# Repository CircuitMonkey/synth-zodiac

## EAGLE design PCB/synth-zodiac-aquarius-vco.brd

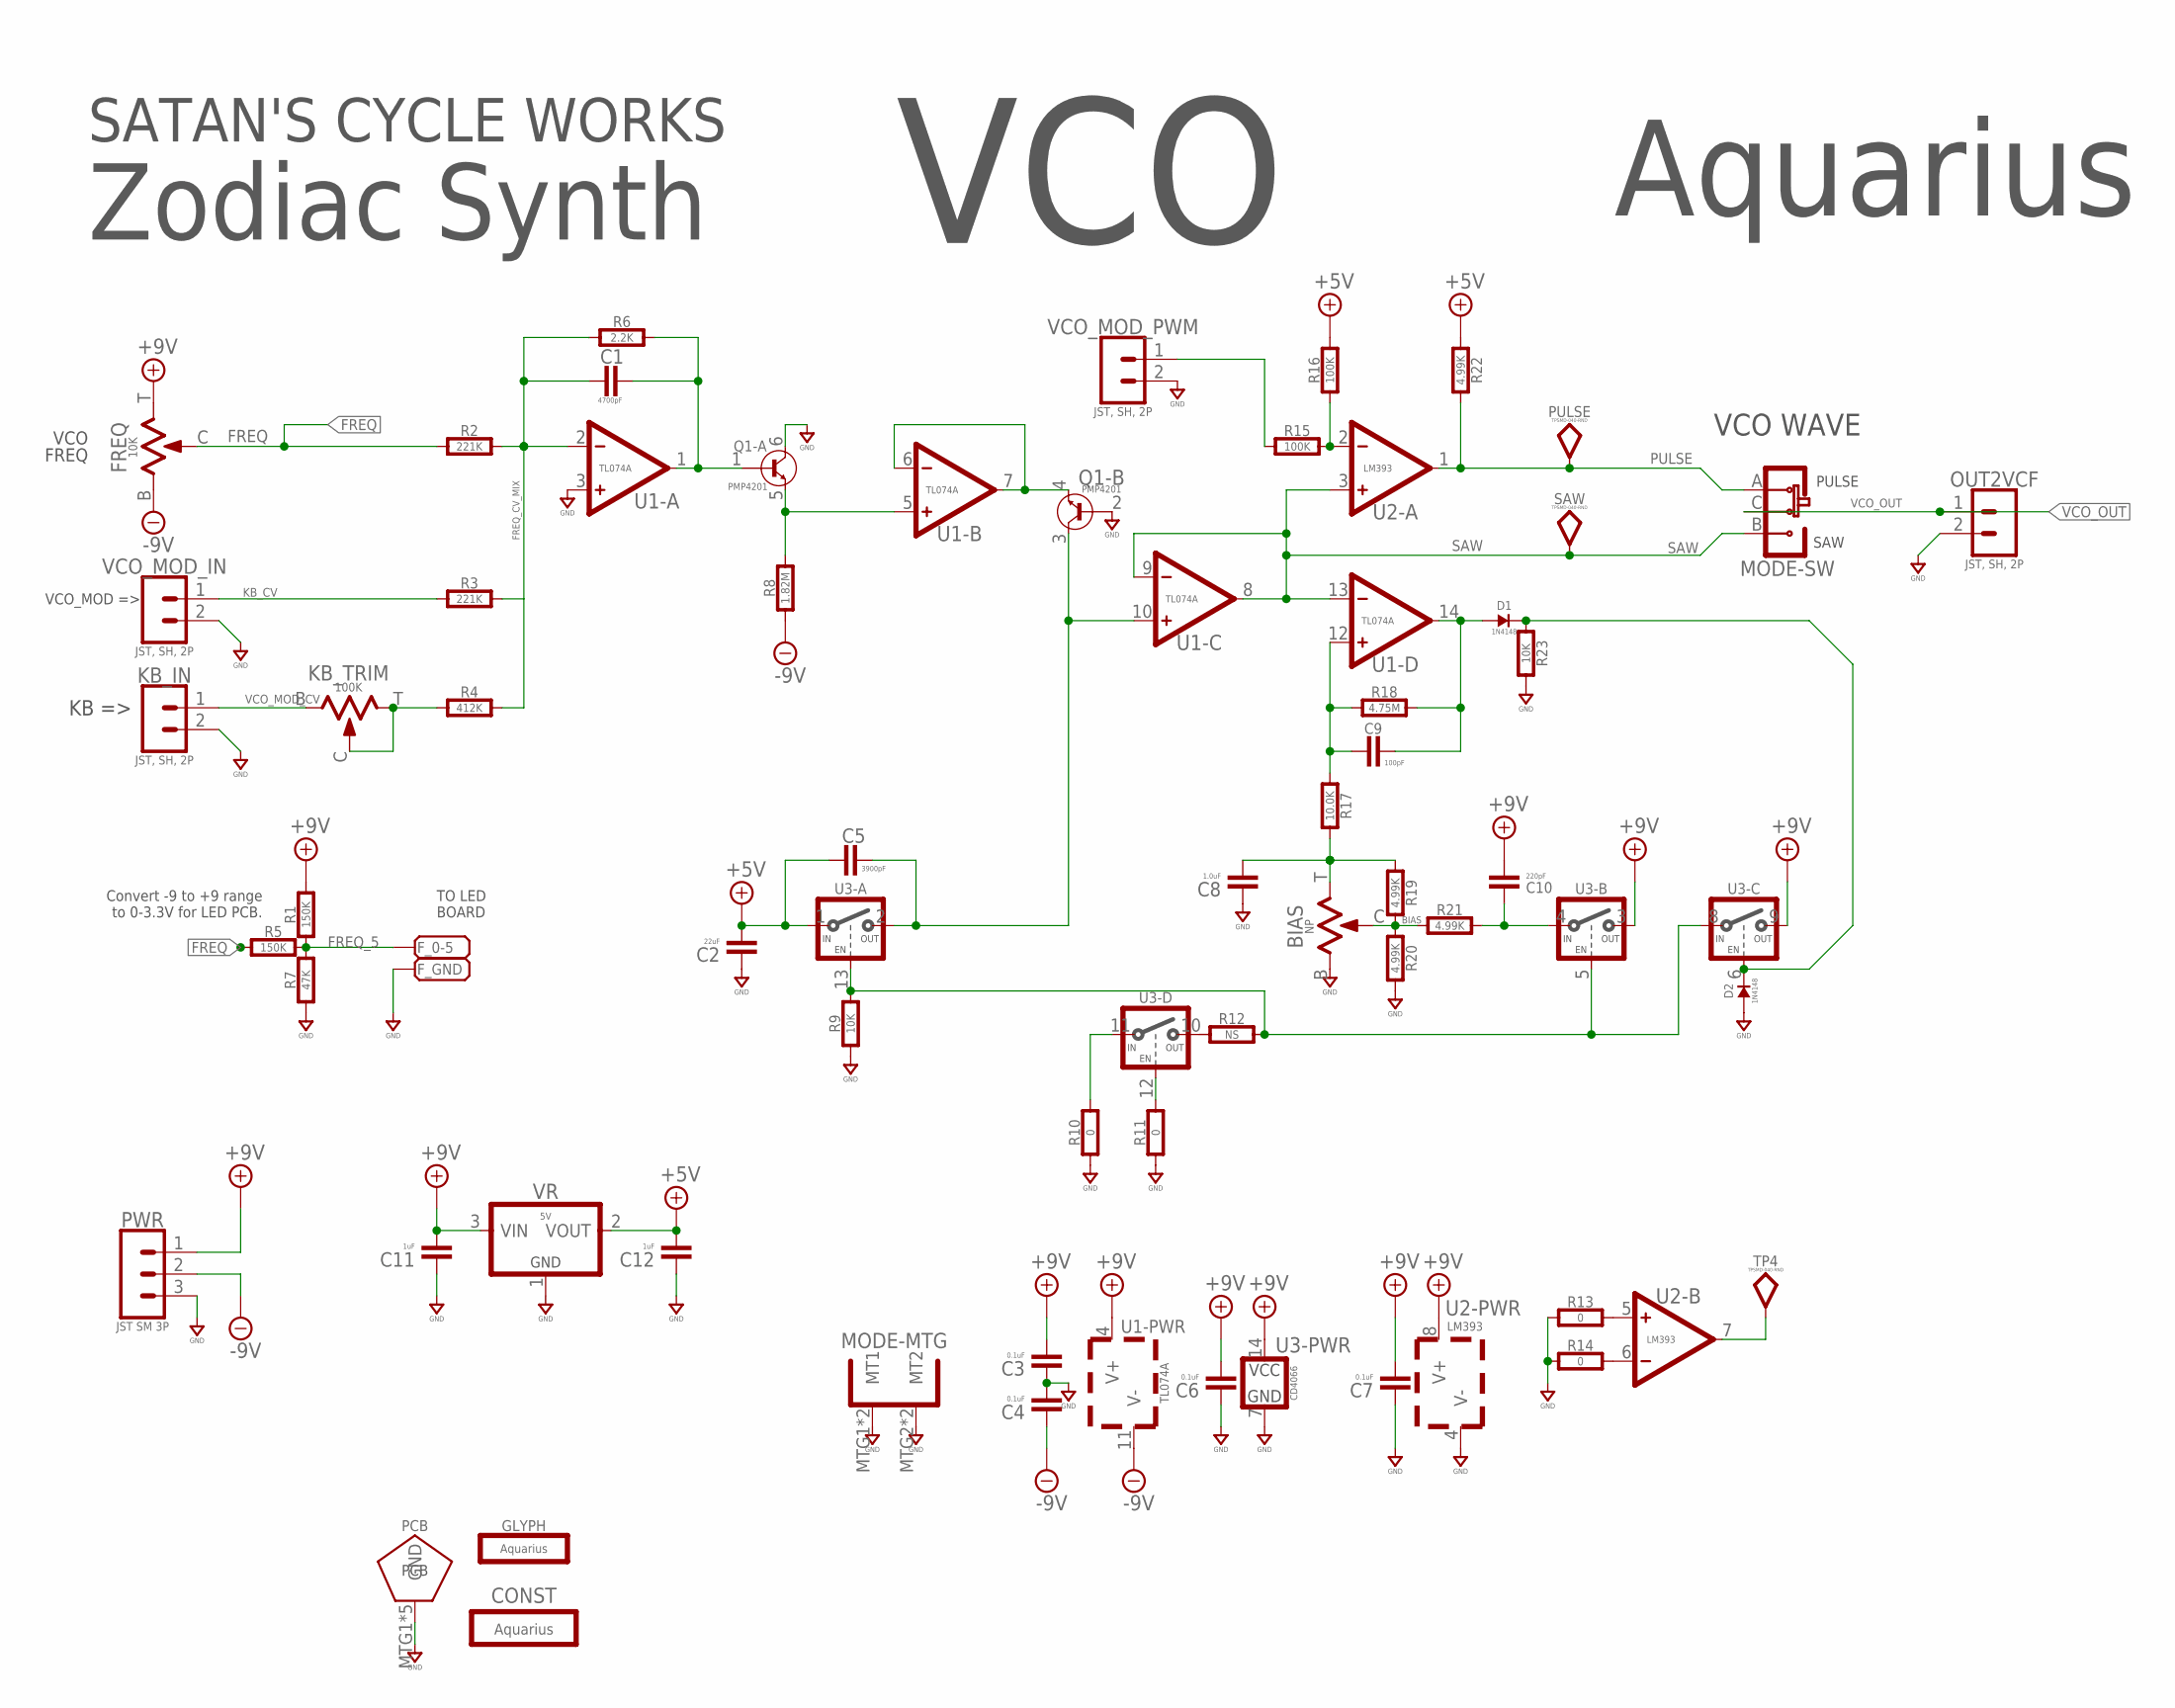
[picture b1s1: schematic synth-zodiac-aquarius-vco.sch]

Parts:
BIAS: NP; TRIM_BOURNS_TC33X
C1: 4700pF; 0603-CAP
C2: 22uF; 0603-CAP
C3, C4, C6, C7: 0.1uF; 0603-CAP
C5: 3900pF; 0603-CAP
C8: 1.0uF; 0603-CAP
C9: 100pF; 0603-CAP
C10: 220pF; 0603-CAP
C11, C12: 1uF; 0603-CAP
CONST: Aquarius; AQUARIUS-CONST
D1, D2: 1N4148; SOD-123
FREQ: 10K; POT-RV9110
F_0-5: PADSMD-070X070; SMD-070MIL
F_GND: PADSMD-070X070; SMD-070MIL
GLYPH: Aquarius; AQUARIUS-GLYPH
KB_IN: JST, SH, 2P; BM02B-SRSS-TB
KB_TRIM: 100K; TRIM_BOURNS_TC33X
MODE: SLIDE-SPDT-MNTSS-12-F45-TH-PCB-2; SS-12-F45-PNL-SMT-2
OUT2VCF: JST, SH, 2P; BM02B-SRSS-TB
PCB: PCB FAB; PENTAGON-40MM-RAD
PULSE: TPSMD-040-RND; SMD-040MIL-RND
PWR: JST SM 3P; BM03B-SRSS-TB
Q1: PMP4201; SOT666
R1, R5: 150K; 0603-RES
R2, R3: 221K; 0603-RES
R4: 412K; 0603-RES
R6: 2.2K; 0603-RES
R7: 47K; 0603-RES
R8: 1.82M; 0603-RES
R9, R23: 10K; 0603-RES
R10, R11, R13, R14: 0; 0603-RES
R12: NS; 0603-RES
R15, R16: 100K; 0603-RES
R17: 10.0K; 0603-RES
R18: 4.75M; 0603-RES
R19, R20, R21, R22: 4.99K; 0603-RES
SAW: TPSMD-040-RND; SMD-040MIL-RND
TP4: TPSMD-040-RND; SMD-040MIL-RND
U1: TL074A; SOP14
U2: LM393; SOP08
U3: CD4066; SOP14
VCO_MOD_IN: JST, SH, 2P; BM02B-SRSS-TB
VCO_MOD_PWM: JST, SH, 2P; BM02B-SRSS-TB
VR: 5V; SOT-23

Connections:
+5V: C2.2, C5.1, C12.2, R16.2, R22.1, U3.1 (IN), VR.2 (VOUT)
+9V: C3.2, C6.2, C7.2, C10.2, C11.2, FREQ.T (3), PWR.1, R1.2, U1.4 (V+), U2.8 (V+), U3.3 (OUT), U3.9 (OUT), U3.14 (VCC), VR.3 (VIN)
-9V: C4.1, FREQ.B (1), PWR.2, R8.1, U1.11 (V-)
BIAS: BIAS.C (2), R19.2, R20.1, R21.1
FREQ: FREQ.C (2), R2.1, R5.1
FREQ_5: F_0-5.1, R1.1, R5.2, R7.2
FREQ_CV_MIX: C1.1, R2.2, R3.2, R4.2, R6.1, U1.2 (-)
GND: BIAS.B (1), C2.1, C3.1, C4.2, C6.1, C7.1, C8.1, C11.1, C12.1, D2.A, F_GND.1, KB_IN.2, MODE.MTG1 (MT1), MODE.MTG2 (MT2), MODE.MTG3 (MT1), MODE.MTG4 (MT2), OUT2VCF.2, PCB.MTG1, PCB.MTG2, PCB.MTG3, PCB.MTG4, PCB.MTG5, PWR.3, Q1.2 (BASE), Q1.6 (COLLECTOR), R7.1, R9.1, R10.1, R11.1, R13.1, R14.1, R20.2, R23.2, U1.3 (+), U2.4 (V-), U3.7 (GND), VCO_MOD_IN.2, VCO_MOD_PWM.2, VR.1 (GND)
KB_CV: KB_IN.1, KB_TRIM.B (1)
unnamed: KB_TRIM.C (2), KB_TRIM.T (3), R4.1
unnamed: Q1.5 (EMITTER), R8.2, U1.5 (+)
unnamed: Q1.4 (EMITTER), U1.6 (-), U1.7 (OUT)
unnamed: C1.2, Q1.1 (BASE), R6.2, U1.1 (OUT)
unnamed: R9.2, R12.2, U3.5 (EN), U3.8 (IN), U3.13 (EN)
unnamed: C9.1, R17.1, R18.1, U1.12 (+)
unnamed: R14.2, U2.6 (-)
unnamed: C9.2, D1.A, R18.2, U1.14 (OUT)
unnamed: C5.2, Q1.3 (COLLECTOR), U1.10 (+), U3.2 (OUT)
unnamed: BIAS.T (3), C8.2, R17.2, R19.1
unnamed: C10.1, R21.2, U3.4 (IN)
unnamed: R12.1, U3.10 (OUT)
unnamed: D1.K, D2.K, R23.1, U3.6 (EN)
unnamed: R10.2, U3.11 (IN)
unnamed: R11.2, U3.12 (EN)
unnamed: R13.2, U2.5 (+)
unnamed: R15.2, R16.1, U2.2 (-)
unnamed: TP4.TP, U2.7 (OUT)
PULSE: MODE.A, PULSE.TP, R22.2, U2.1 (OUT)
PWM_CV: R15.1, VCO_MOD_PWM.1
SAW: MODE.B, SAW.TP, U1.8 (OUT), U1.9 (-), U1.13 (-), U2.3 (+)
VCO_MOD_CV: R3.1, VCO_MOD_IN.1
VCO_OUT: MODE.C, OUT2VCF.1

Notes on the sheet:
VCO FREQ
VCO WAVE
VCO
PULSE
SAW
KB =>
VCO_MOD =>
Zodiac Synth
Aquarius
TO LED BOARD
Convert -9 to +9 range to 0-3.3V for LED PCB.
SATAN'S CYCLE WORKS

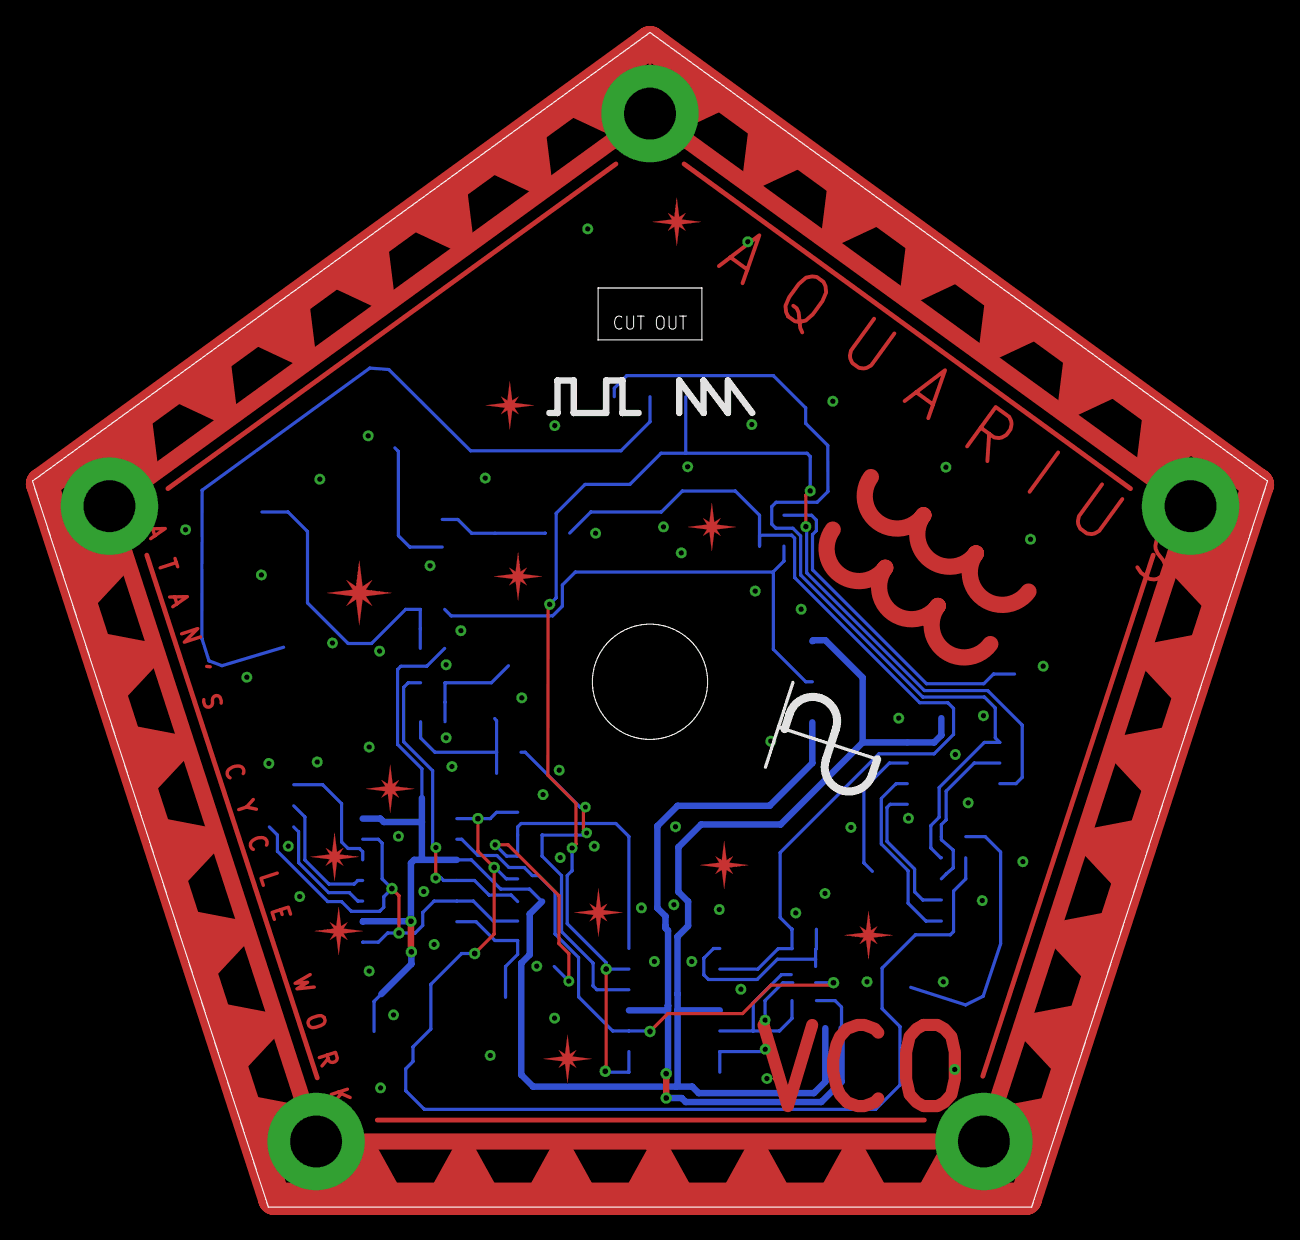
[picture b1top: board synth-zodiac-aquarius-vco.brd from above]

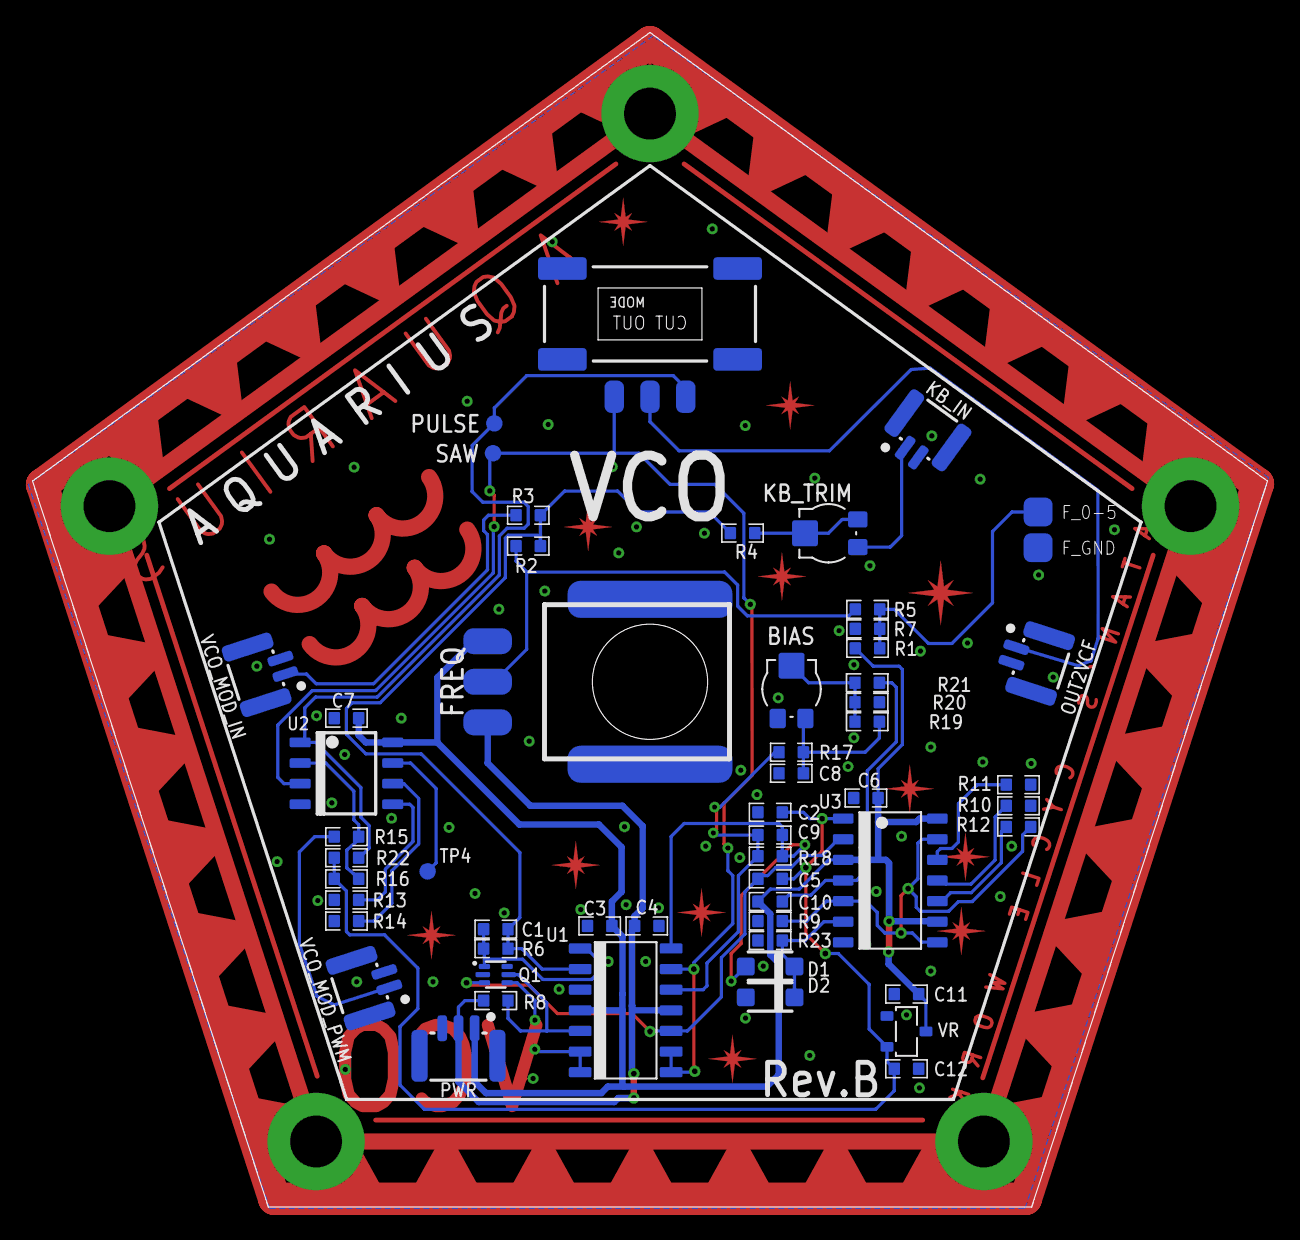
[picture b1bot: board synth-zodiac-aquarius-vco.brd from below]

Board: 2 copper layers, 76.1 x 72.4 mm, 59 parts (55 on the bottom side), 32 nets.

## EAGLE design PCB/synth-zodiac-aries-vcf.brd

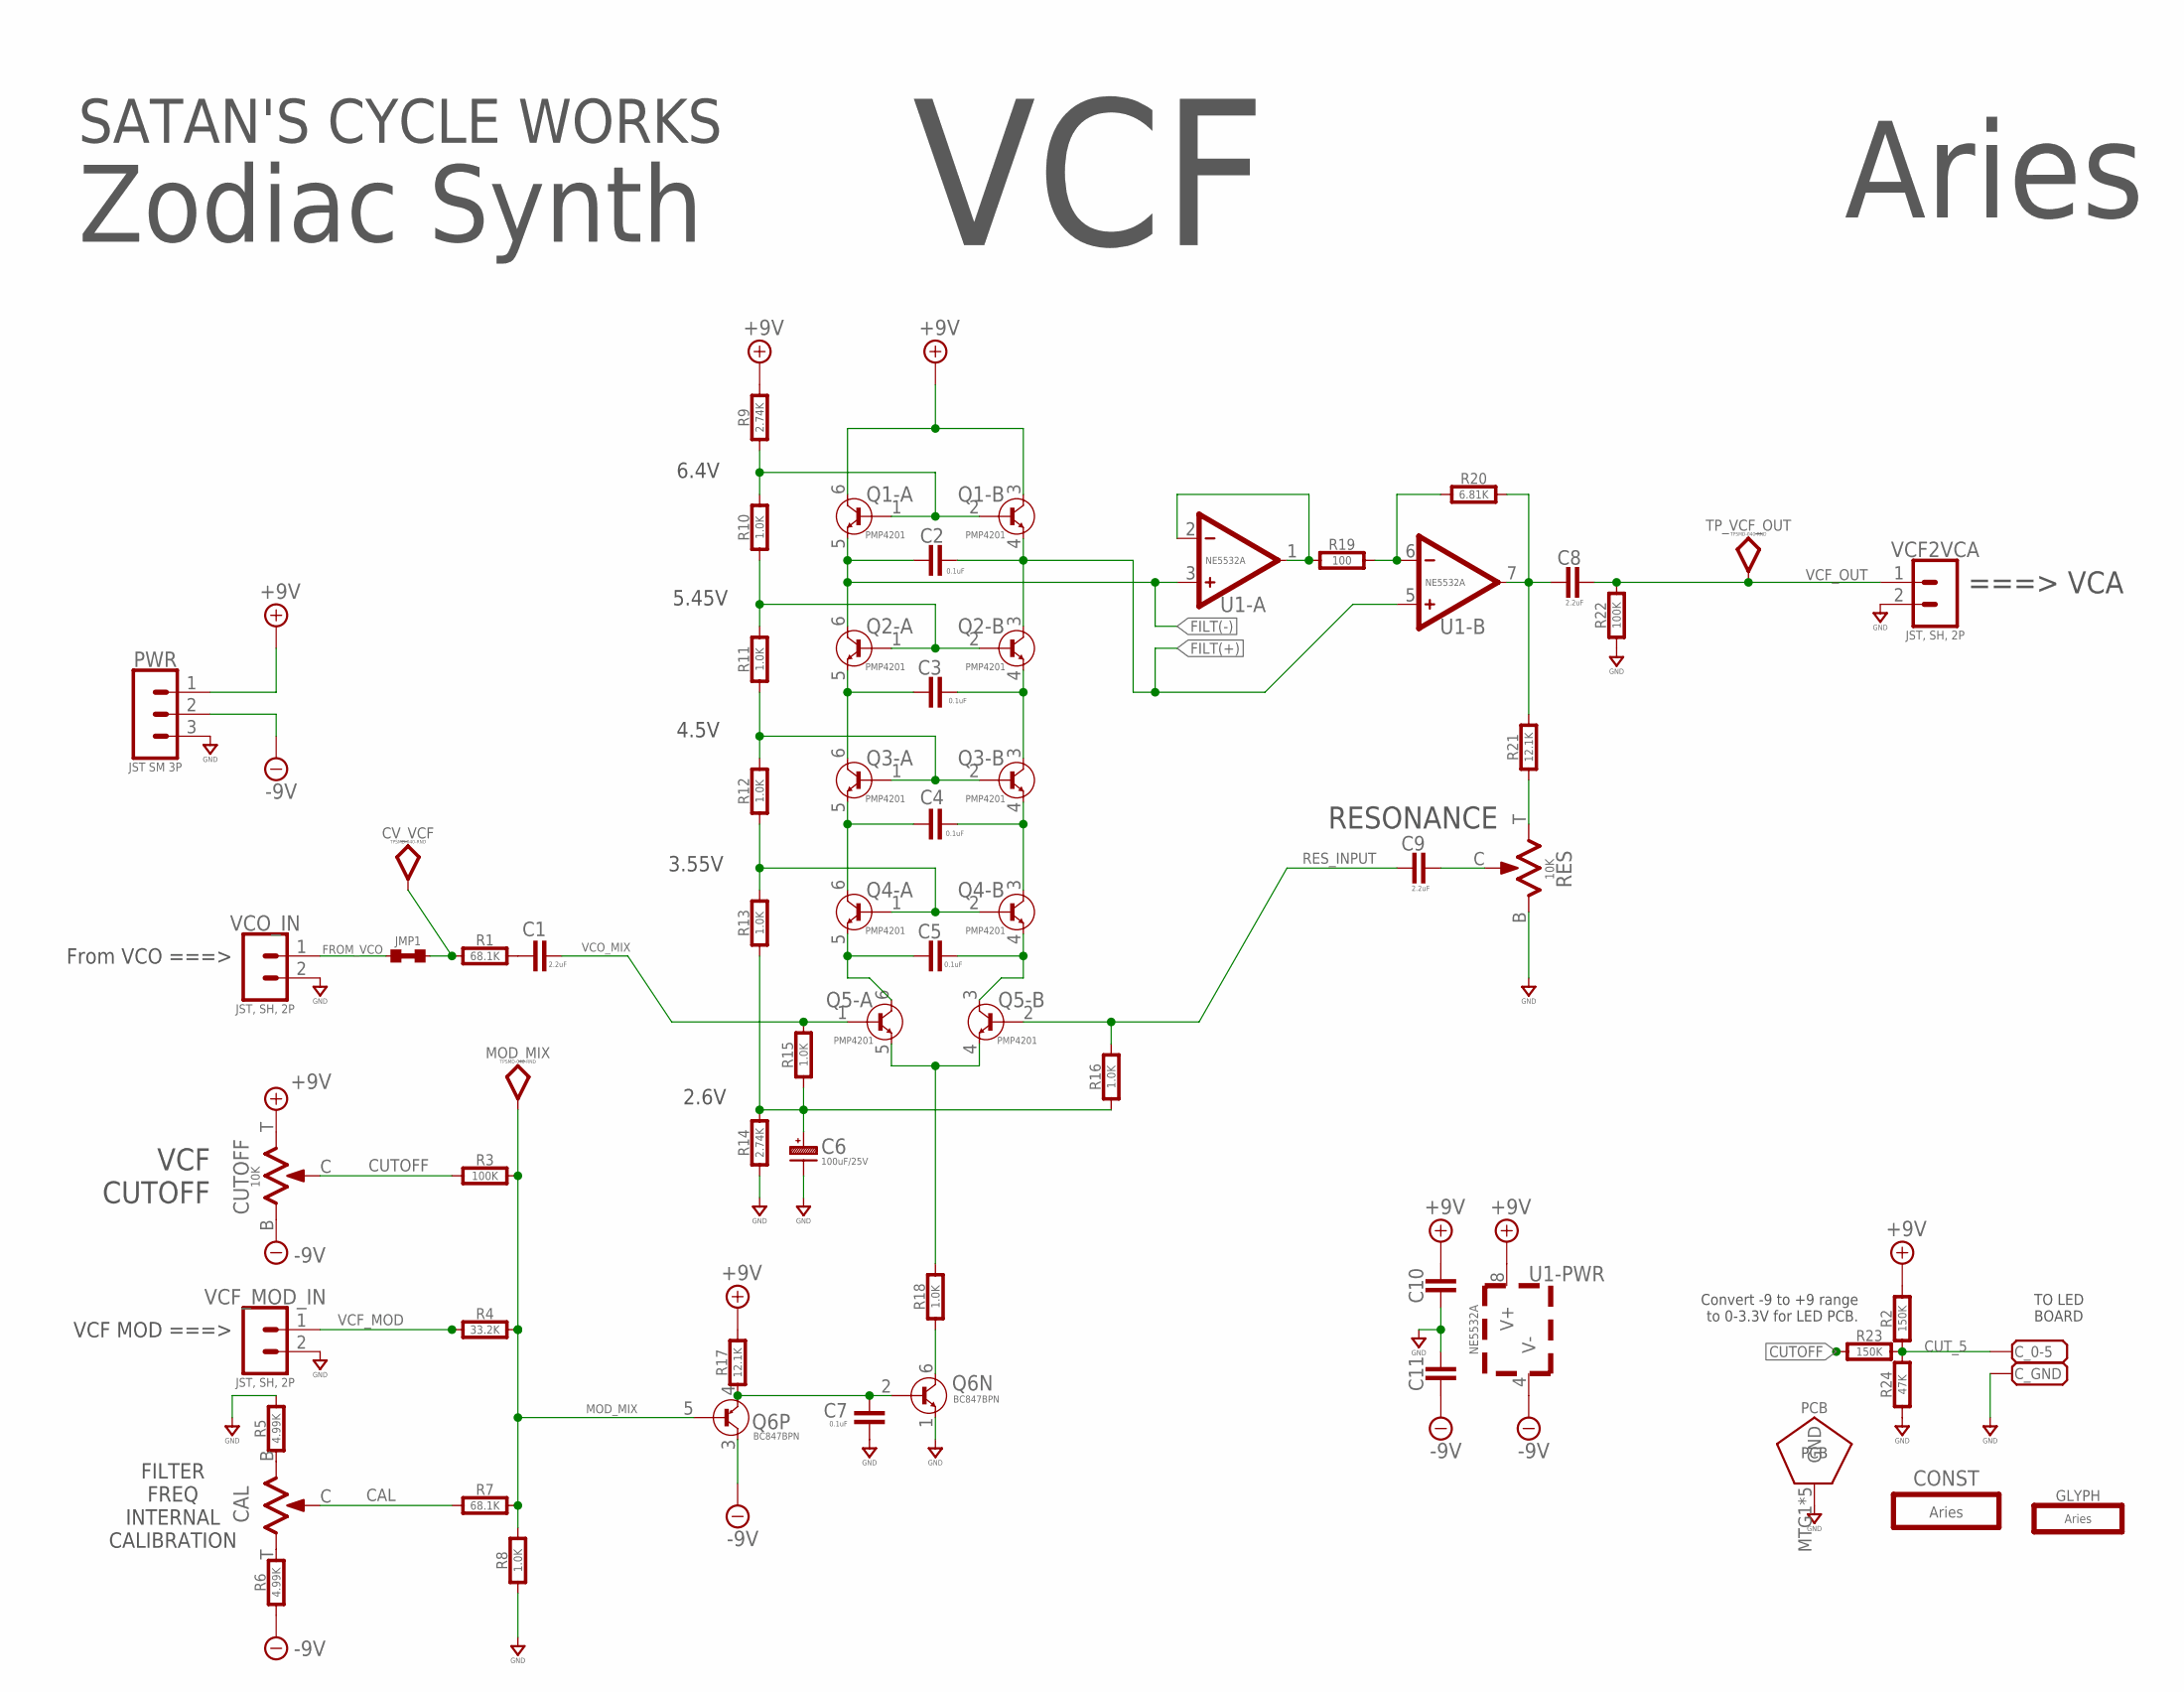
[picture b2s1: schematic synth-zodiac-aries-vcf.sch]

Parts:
C1, C8, C9: 2.2uF; 0603-CAP
C2, C3, C4, C5, C7, C10, C11: 0.1uF; 0603-CAP
C6: 100uF/25V; CAP_ALUM_SMT_6.3; MPN 865090445008
CAL: 10K; TRIM_BOURNS_TC33X
CONST: Aries; ARIES-CONST
CUTOFF: 10K; POT-RV9110
CV_VCF: TPSMD-040-RND; SMD-040MIL-RND
C_0-5: PADSMD-070X070; SMD-070MIL
C_GND: PADSMD-070X070; SMD-070MIL
GLYPH: Aries; ARIES-GLYPH
JMP1: NP; 0603-SHORT
MOD_MIX: TPSMD-040-RND; SMD-040MIL-RND
PCB: PCB FAB; PENTAGON-40MM-RAD
PWR: JST SM 3P; BM03B-SRSS-TB
Q1, Q2, Q3, Q4, Q5: PMP4201; SOT666
Q6: BC847BPN; SOT363
R1, R7: 68.1K; 0603-RES
R2, R23: 150K; 0603-RES
R3, R22: 100K; 0603-RES
R4: 33.2K; 0603-RES
R5, R6: 4.99K; 0603-RES
R8, R10, R11, R12, R13, R15, R16, R18: 1.0K; 0603-RES
R9, R14: 2.74K; 0603-RES
R17, R21: 12.1K; 0603-RES
R19: 100; 0603-RES
R20: 6.81K; 0603-RES
R24: 47K; 0603-RES
RES: 10K; POT-RV9110
TP_VCF_OUT: TPSMD-040-RND; SMD-040MIL-RND
U1: NE5532A; SOP08
VCF2VCA: JST, SH, 2P; BM02B-SRSS-TB
VCF_MOD_IN: JST, SH, 2P; BM02B-SRSS-TB
VCO_IN: JST, SH, 2P; BM02B-SRSS-TB

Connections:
+9V: C10.2, CUTOFF.T (3), PWR.1, Q1.3 (COLLECTOR), Q1.6 (COLLECTOR), R2.2, R9.2, R17.2, U1.8 (V+)
-9V: C11.1, CUTOFF.B (1), PWR.2, Q6.3 (COLLECTOR), R6.1, U1.4 (V-)
CAL: CAL.C (2), R7.1
CUTOFF: CUTOFF.C (2), R3.1, R23.1
CUT_5: C_0-5.1, R2.1, R23.2, R24.2
FILT(+): C2.2, Q1.4 (EMITTER), Q2.3 (COLLECTOR), U1.5 (+)
FILT(-): C2.1, Q1.5 (EMITTER), Q2.6 (COLLECTOR), U1.3 (+)
FROM_VCO: JMP1.3 (1), VCO_IN.1
GND: C6.- (N), C7.2, C10.1, C11.2, C_GND.1, PCB.MTG1, PCB.MTG2, PCB.MTG3, PCB.MTG4, PCB.MTG5, PWR.3, Q6.1 (EMITTER), R5.2, R8.1, R14.1, R22.1, R24.1, RES.B (1), VCF2VCA.2, VCF_MOD_IN.2, VCO_IN.2
MOD_MIX: MOD_MIX.TP, Q6.5 (BASE), R3.2, R4.2, R7.2, R8.2
unnamed: R19.2, R20.1, U1.6 (-)
unnamed: Q1.1 (BASE), Q1.2 (BASE), R9.1, R10.2
unnamed: C3.1, Q2.5 (EMITTER), Q3.6 (COLLECTOR)
unnamed: C3.2, Q2.4 (EMITTER), Q3.3 (COLLECTOR)
unnamed: Q2.1 (BASE), Q2.2 (BASE), R10.1, R11.2
unnamed: C4.1, Q3.5 (EMITTER), Q4.6 (COLLECTOR)
unnamed: C4.2, Q3.4 (EMITTER), Q4.3 (COLLECTOR)
unnamed: Q3.1 (BASE), Q3.2 (BASE), R11.1, R12.2
unnamed: C5.1, Q4.5 (EMITTER), Q5.6 (COLLECTOR)
unnamed: C5.2, Q4.4 (EMITTER), Q5.3 (COLLECTOR)
unnamed: Q4.1 (BASE), Q4.2 (BASE), R12.1, R13.2
unnamed: Q5.4 (EMITTER), Q5.5 (EMITTER), R18.2
unnamed: Q6.6 (COLLECTOR), R18.1
unnamed: C6.+, R13.1, R14.2, R15.1, R16.1
unnamed: C7.1, Q6.2 (BASE), Q6.4 (EMITTER), R17.1
unnamed: CAL.T (3), R6.2
unnamed: CAL.B (1), R5.1
unnamed: C1.1, R1.2
unnamed: R19.1, U1.1 (OUT), U1.2 (-)
unnamed: C8.1, R20.2, R21.2, U1.7 (OUT)
unnamed: R21.1, RES.T (3)
unnamed: C9.2, RES.C (2)
RES_INPUT: C9.1, Q5.2 (BASE), R16.2
VCF_IN: CV_VCF.TP, JMP1.4 (2), R1.1
VCF_MOD: R4.1, VCF_MOD_IN.1
VCF_OUT: C8.2, R22.2, TP_VCF_OUT.TP, VCF2VCA.1
VCO_MIX: C1.2, Q5.1 (BASE), R15.2

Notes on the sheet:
FILTER FREQ INTERNAL CALIBRATION
RESONANCE
VCF CUTOFF
===> VCA
From VCO ===>
VCF MOD ===>
6.4V
5.45V
4.5V
3.55V
2.6V
TO LED BOARD
Convert -9 to +9 range to 0-3.3V for LED PCB.
VCF
Zodiac Synth
Aries
SATAN'S CYCLE WORKS

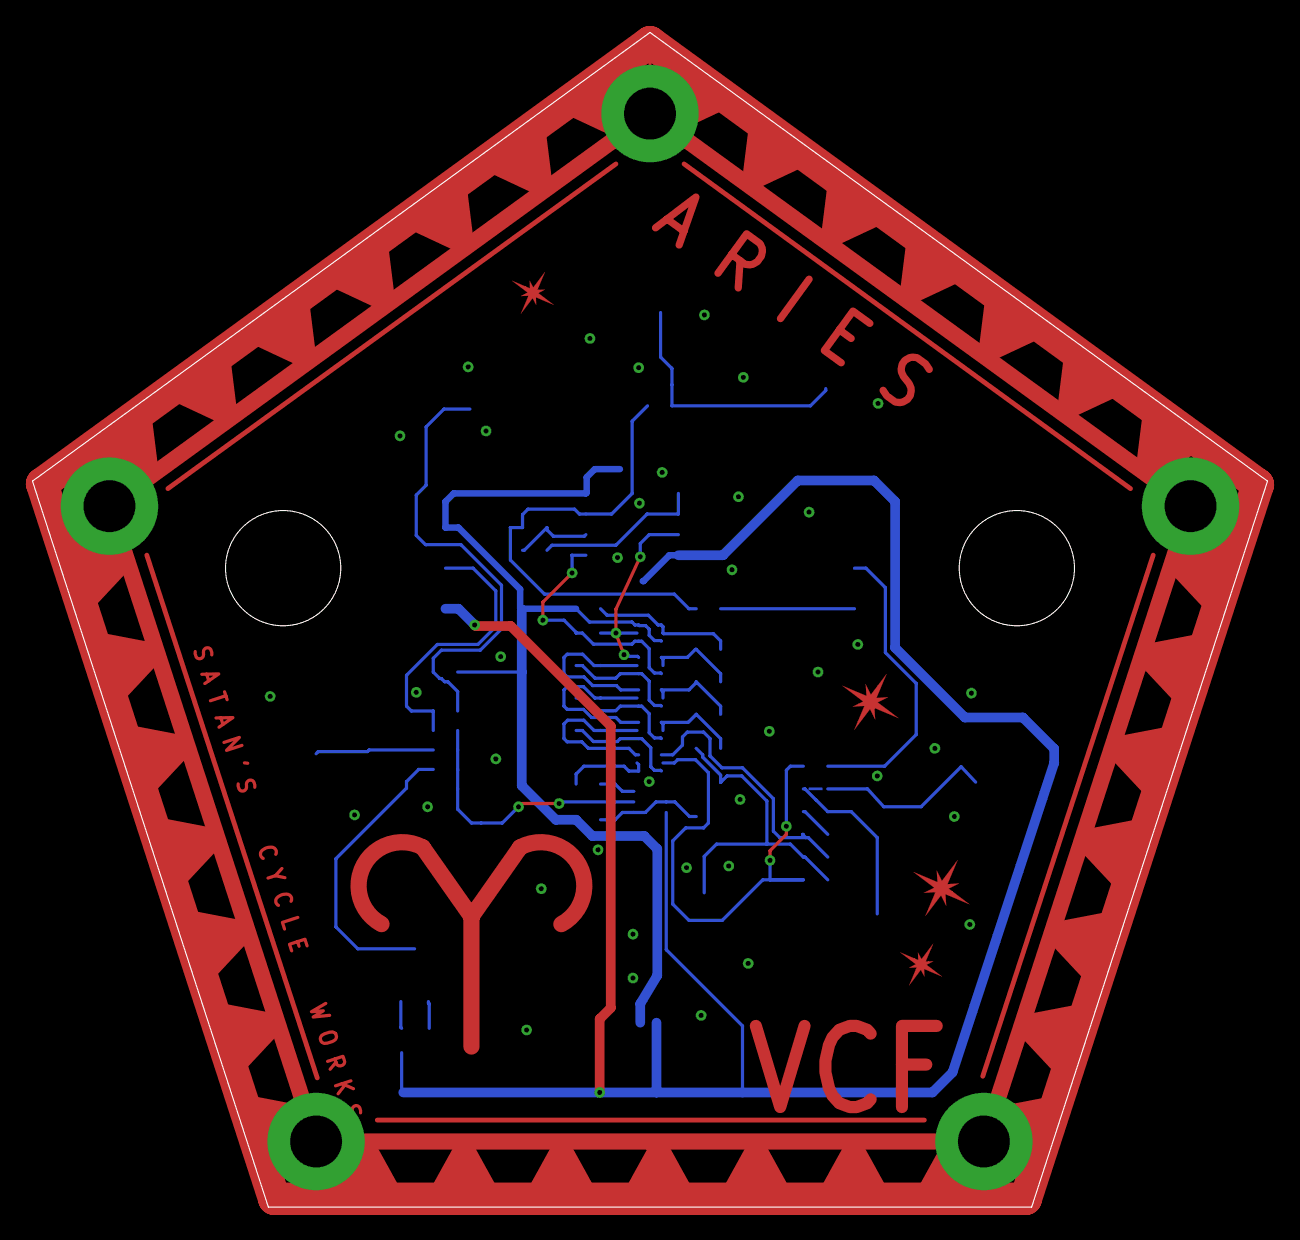
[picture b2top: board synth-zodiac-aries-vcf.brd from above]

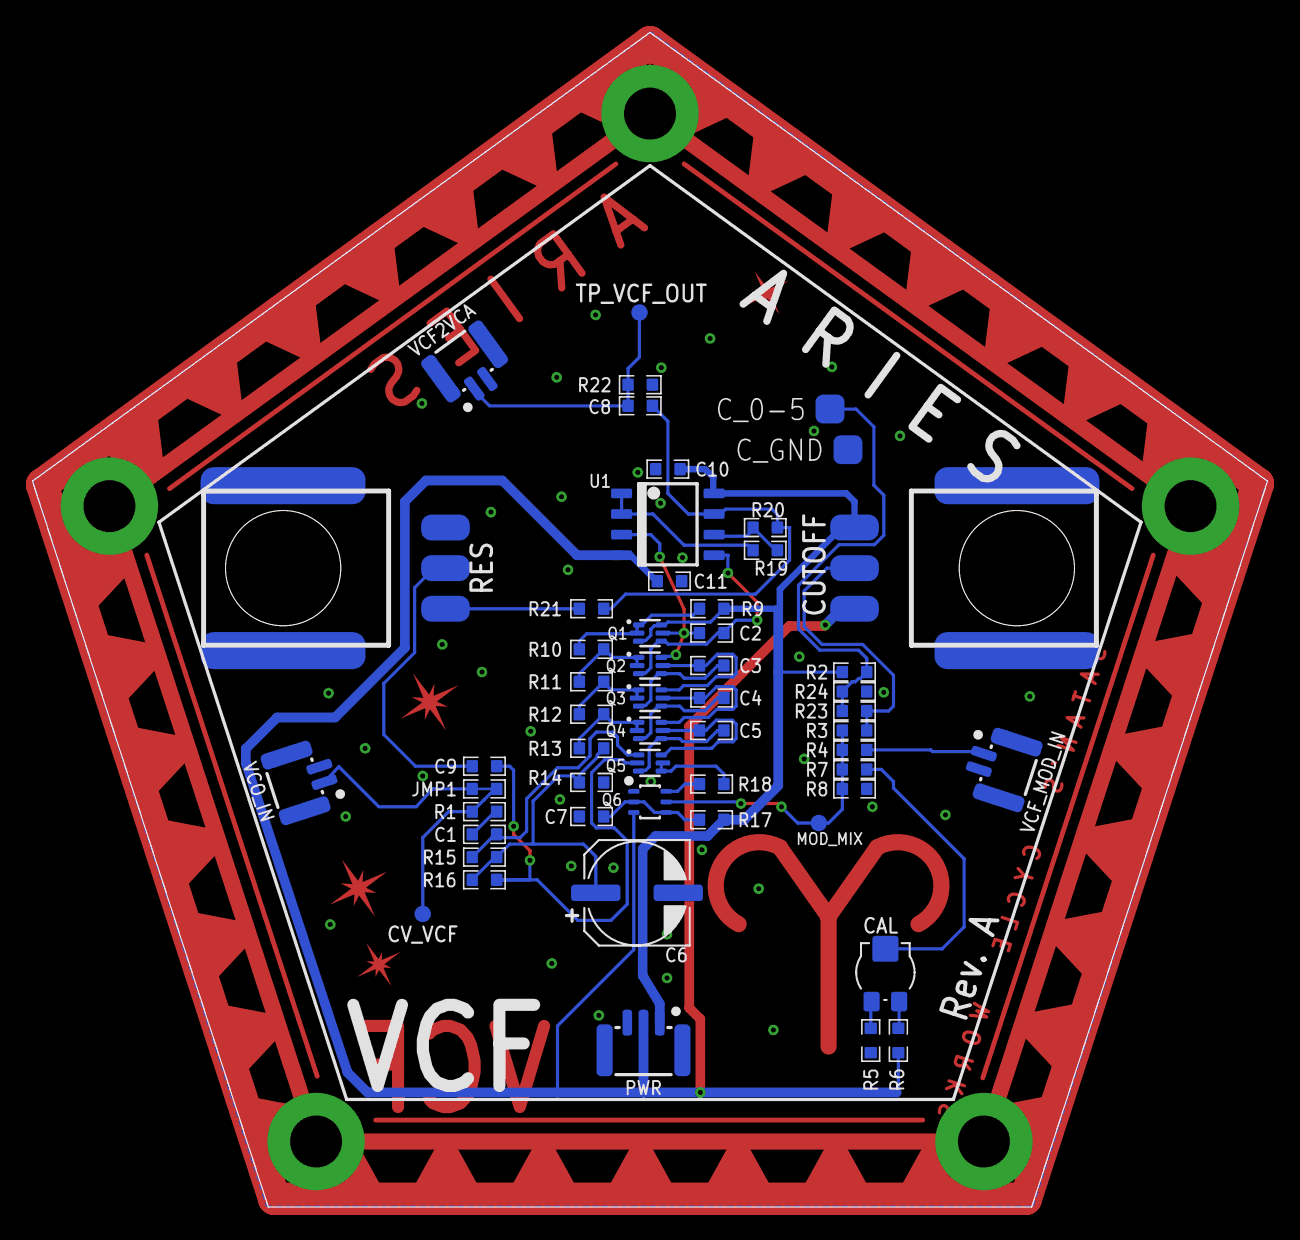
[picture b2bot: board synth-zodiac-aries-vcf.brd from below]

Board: 2 copper layers, 76.1 x 72.4 mm, 58 parts (55 on the bottom side), 37 nets.

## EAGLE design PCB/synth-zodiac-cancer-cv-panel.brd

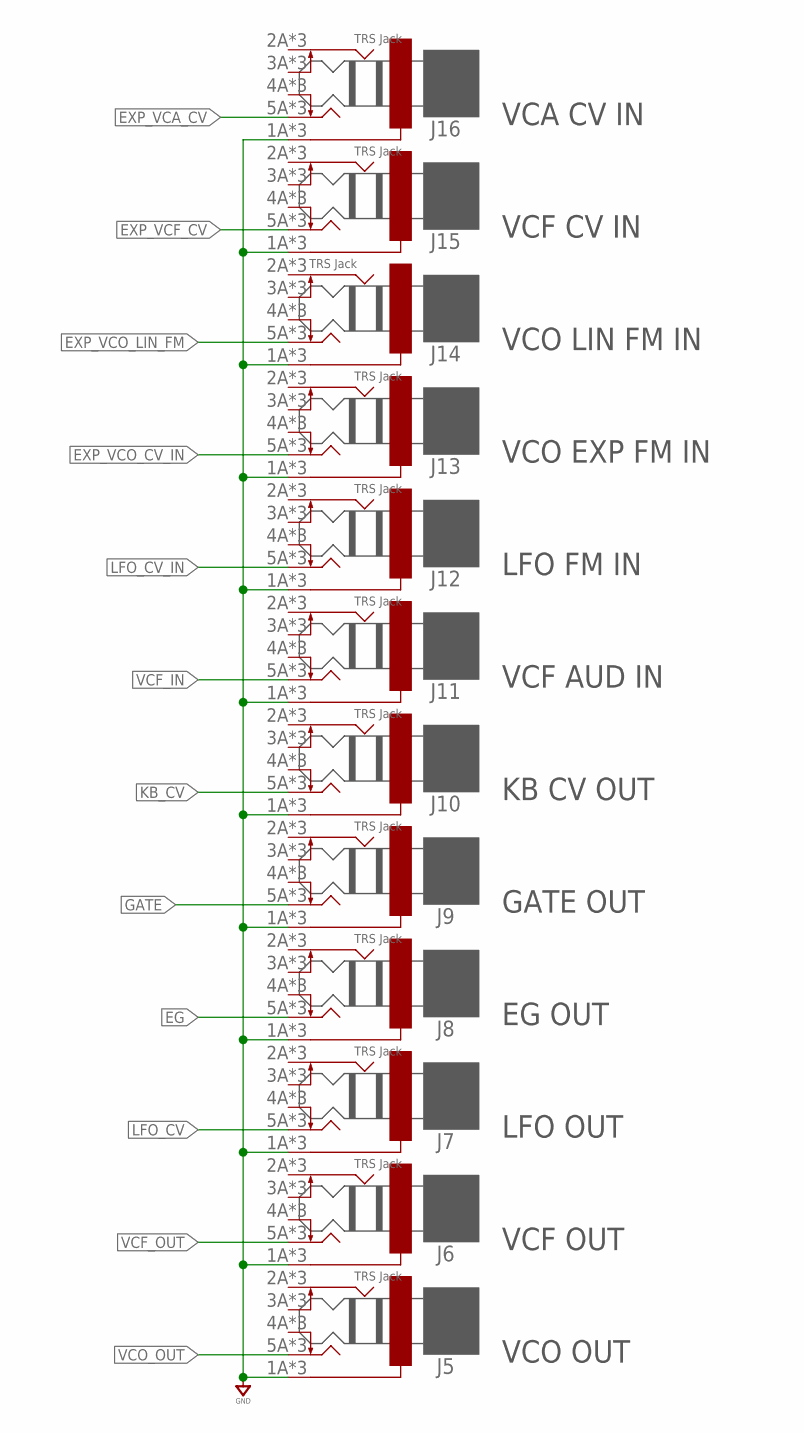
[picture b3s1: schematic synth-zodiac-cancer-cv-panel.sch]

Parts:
J5, J6, J7, J8, J9, J10, J11, J12, J13, J14, J15, J16: TRS Jack; PJ-324

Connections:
EG: J8.5A (T), J8.5A1 (T), J8.5A2 (T)
EXP_VCA_CV: J16.5A (T), J16.5A1 (T), J16.5A2 (T)
EXP_VCF_CV: J15.5A (T), J15.5A1 (T), J15.5A2 (T)
EXP_VCO_CV_IN: J13.5A (T), J13.5A1 (T), J13.5A2 (T)
EXP_VCO_LIN_FM: J14.5A (T), J14.5A1 (T), J14.5A2 (T)
GATE: J9.5A (T), J9.5A1 (T), J9.5A2 (T)
GND: J5.1A (S), J5.1A1 (S), J5.1A2 (S), J6.1A (S), J6.1A1 (S), J6.1A2 (S), J7.1A (S), J7.1A1 (S), J7.1A2 (S), J8.1A (S), J8.1A1 (S), J8.1A2 (S), J9.1A (S), J9.1A1 (S), J9.1A2 (S), J10.1A (S), J10.1A1 (S), J10.1A2 (S), J11.1A (S), J11.1A1 (S), J11.1A2 (S), J12.1A (S), J12.1A1 (S), J12.1A2 (S), J13.1A (S), J13.1A1 (S), J13.1A2 (S), J14.1A (S), J14.1A1 (S), J14.1A2 (S), J15.1A (S), J15.1A1 (S), J15.1A2 (S), J16.1A (S), J16.1A1 (S), J16.1A2 (S)
KB_CV: J10.5A (T), J10.5A1 (T), J10.5A2 (T)
LFO_CV: J7.5A (T), J7.5A1 (T), J7.5A2 (T)
LFO_CV_IN: J12.5A (T), J12.5A1 (T), J12.5A2 (T)
VCF_IN: J11.5A (T), J11.5A1 (T), J11.5A2 (T)
VCF_OUT: J6.5A (T), J6.5A1 (T), J6.5A2 (T)
VCO_OUT: J5.5A (T), J5.5A1 (T), J5.5A2 (T)

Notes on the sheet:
VCA CV IN VCF CV IN VCO LIN FM IN VCO EXP FM IN LFO FM IN VCF AUD IN KB CV OUT GATE OUT EG OUT LFO OUT VCF OUT VCO OUT

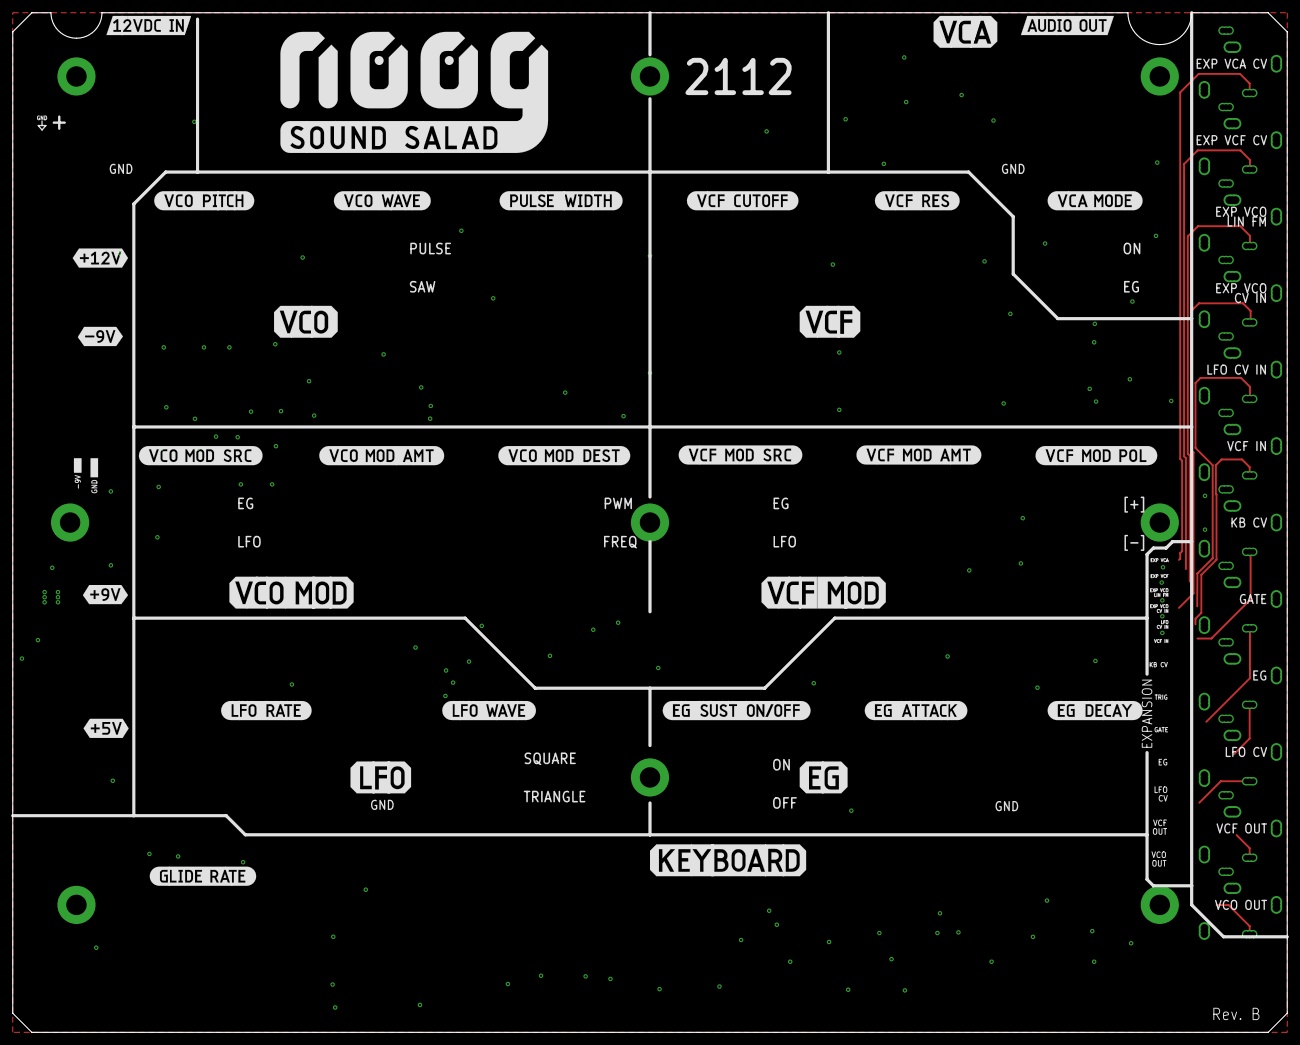
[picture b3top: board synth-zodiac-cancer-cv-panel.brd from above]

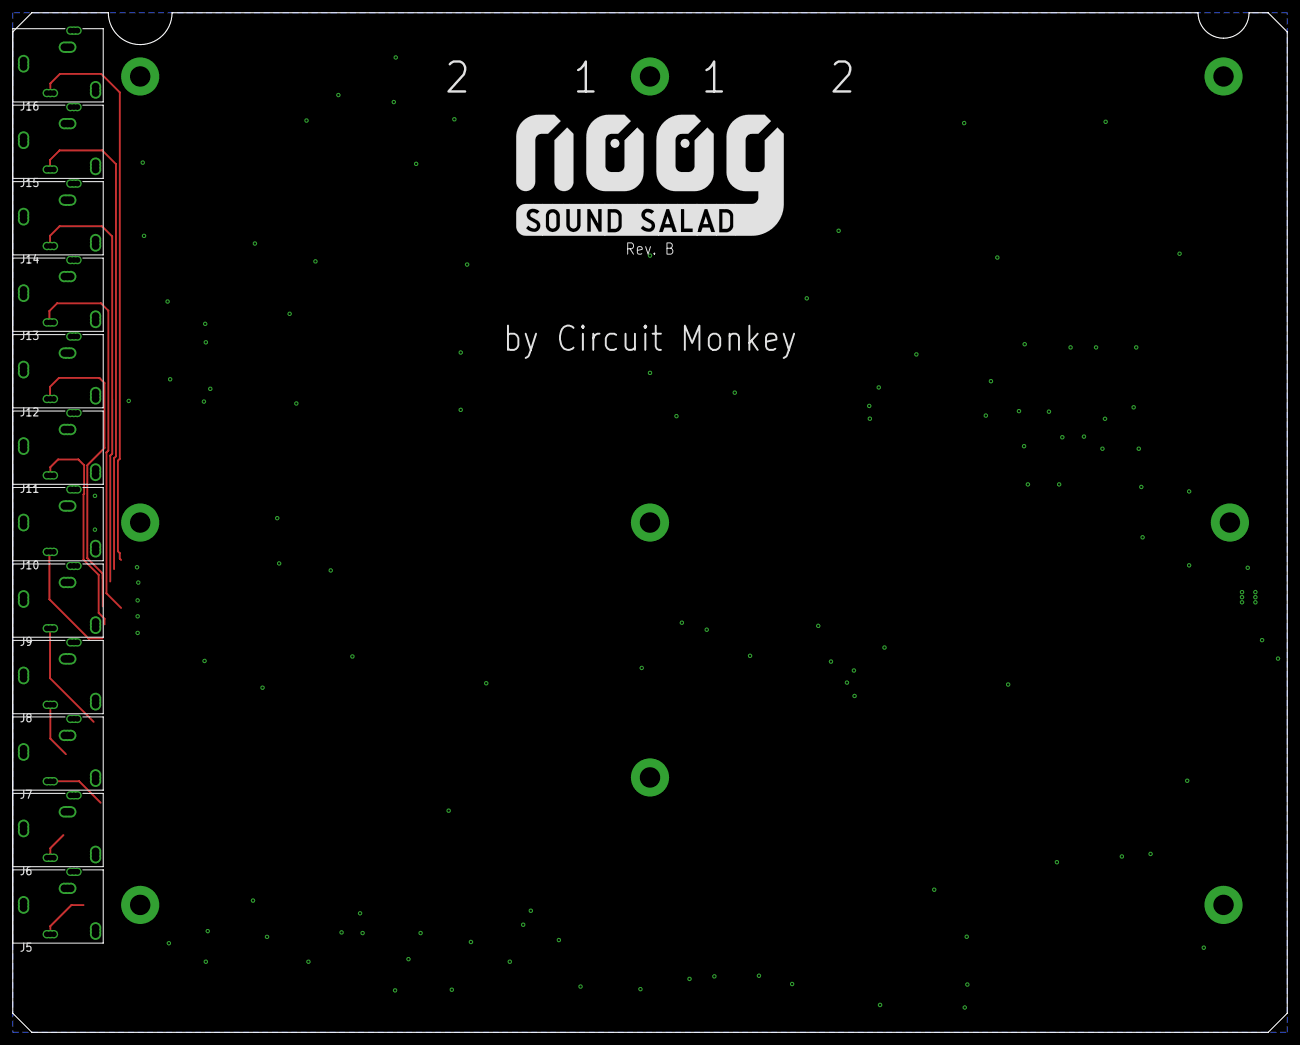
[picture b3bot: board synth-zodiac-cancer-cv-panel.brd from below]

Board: 2 copper layers, 200.0 x 160.0 mm, 12 parts (12 on the bottom side), 13 nets.
